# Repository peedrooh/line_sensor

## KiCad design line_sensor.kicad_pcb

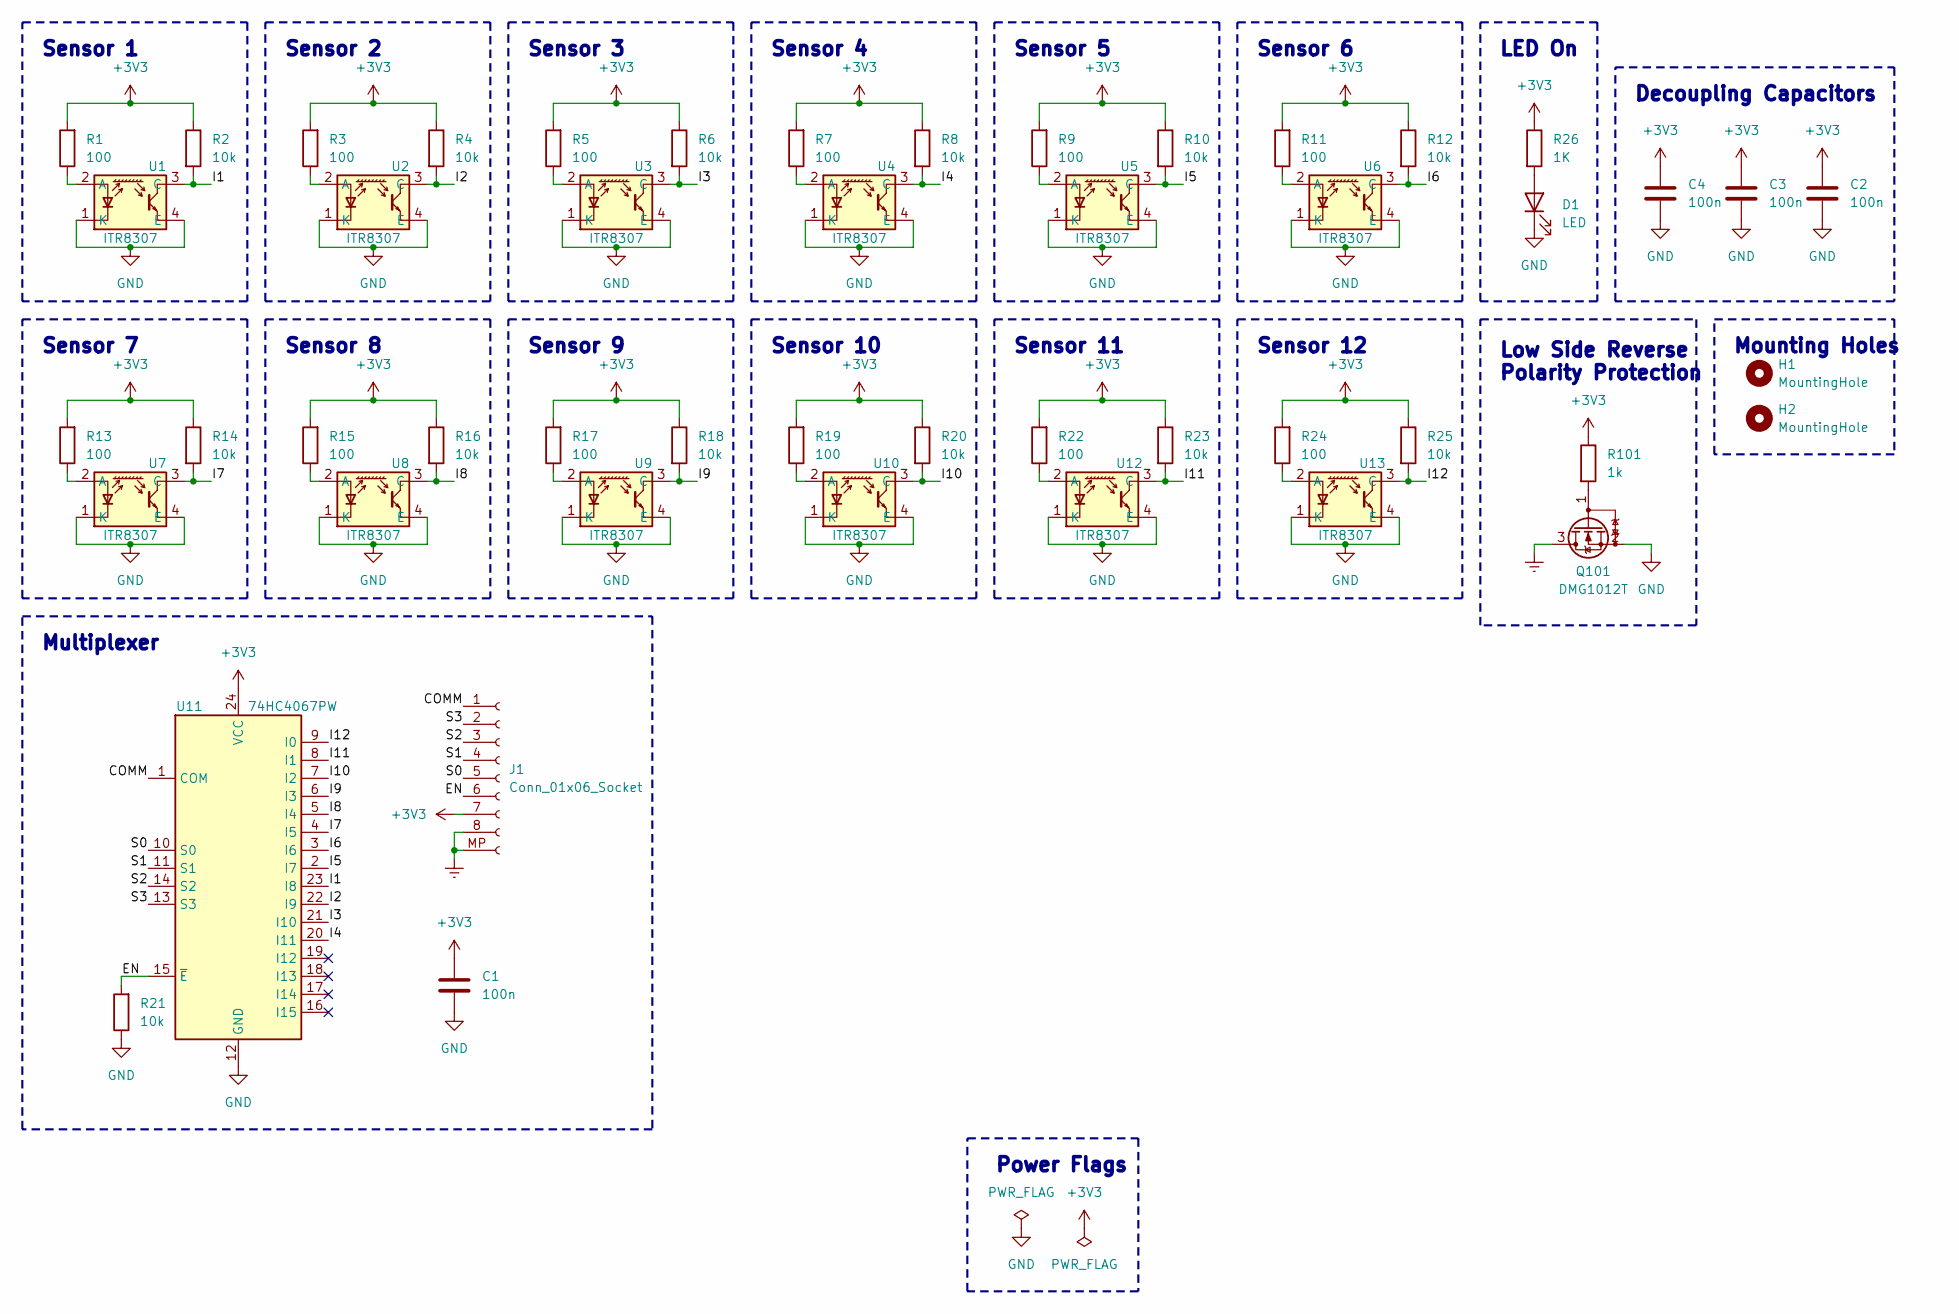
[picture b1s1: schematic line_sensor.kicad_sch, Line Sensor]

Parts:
C1, C2, C3, C4: 100n; C_0805_2012Metric_Pad1.18x1.45mm_HandSolder; LCSC C38141
D1: LED; LED_0805_2012Metric; LCSC C391863
H1, H2: MountingHole; MountingHole_3.2mm_M3_Pad_Via
J1: Conn_01x06_Socket; JST_PH_B8B-PH-SM4-TB_1x08-1MP_P2.00mm_Vertical
Q101: DMG1012T; SOT-523; LCSC C20512
R1, R3, R5, R7, R9, R11, R13, R15, R17, R19, R22, R24: 100; R_0805_2012Metric; LCSC C17408
R2, R4, R8, R10, R12, R14, R16, R18, R20, R21, R23, R25: 10k; R_0805_2012Metric; LCSC C17414
R6: 10k; R_0805_2012Metric; MPN C17414
R26: 1K; R_0805_2012Metric; LCSC C17513
R101: 1k; R_0805_2012Metric; LCSC C17513
U1, U2, U3, U4, U5, U6, U7, U8, U9, U10, U12, U13: ITR8307; ITR8307_S18_TR8_B; LCSC C115037
U11: 74HC4067PW; TSSOP-24_4.4x7.8mm_P0.65mm; LCSC C179326

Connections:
+3V3: C1.1, C2.1, C3.1, C4.1, J1.7, R1.2, R2.1, R3.2, R4.1, R5.2, R6.1, R7.2, R8.1, R9.2, R10.1, R11.2, R12.1, R13.2, R14.1, R15.2, R16.1, R17.2, R18.1, R19.2, R20.1, R22.2, R23.1, R24.2, R25.1, R26.1, R101.1, U11.24 (VCC)
/COMM: J1.1, U11.1 (COM)
/EN: J1.6, R21.2, U11.15 (~E)
/I1: R2.2, U1.3 (C), U11.23 (I8)
/I2: R4.2, U2.3 (C), U11.22 (I9)
/I3: R6.2, U3.3 (C), U11.21 (I10)
/I4: R8.2, U4.3 (C), U11.20 (I11)
/I5: R10.2, U5.3 (C), U11.2 (I7)
/I6: R12.2, U6.3 (C), U11.3 (I6)
/I7: R14.2, U7.3 (C), U11.4 (I5)
/I8: R16.2, U8.3 (C), U11.5 (I4)
/I9: R18.2, U9.3 (C), U11.6 (I3)
/I10: R20.2, U10.3 (C), U11.7 (I2)
/I11: R23.2, U11.8 (I1), U12.3 (C)
/I12: R25.2, U11.9 (I0), U13.3 (C)
/S0: J1.5, U11.10 (S0)
/S1: J1.4, U11.11 (S1)
/S2: J1.3, U11.14 (S2)
/S3: J1.2, U11.13 (S3)
Earth: J1.8, J1.MP (Pin_9), Q101.3 (D)
GND: C1.2, C2.2, C3.2, C4.2, D1.1 (K), Q101.2 (S), R21.1, U1.1 (K), U1.4 (E), U2.1 (K), U2.4 (E), U3.1 (K), U3.4 (E), U4.1 (K), U4.4 (E), U5.1 (K), U5.4 (E), U6.1 (K), U6.4 (E), U7.1 (K), U7.4 (E), U8.1 (K), U8.4 (E), U9.1 (K), U9.4 (E), U10.1 (K), U10.4 (E), U11.12 (GND), U12.1 (K), U12.4 (E), U13.1 (K), U13.4 (E)
unnamed: D1.2 (A), R26.2
unnamed: Q101.1 (G), R101.2
unnamed: R1.1, U1.2 (A)
unnamed: R3.1, U2.2 (A)
unnamed: R5.1, U3.2 (A)
unnamed: R7.1, U4.2 (A)
unnamed: R9.1, U5.2 (A)
unnamed: R11.1, U6.2 (A)
unnamed: R13.1, U7.2 (A)
unnamed: R15.1, U8.2 (A)
unnamed: R17.1, U9.2 (A)
unnamed: R19.1, U10.2 (A)
unnamed: R22.1, U12.2 (A)
unnamed: R24.1, U13.2 (A)

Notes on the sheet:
Sensor 7
Sensor 10
Mounting Holes
LED On
Sensor 11
Power Flags
Sensor 4
Sensor 2
Sensor 12
Sensor 3
Sensor 5
Decoupling Capacitors
Multiplexer
Low Side Reverse Polarity Protection
Sensor 6
Sensor 9
Sensor 1
Sensor 8

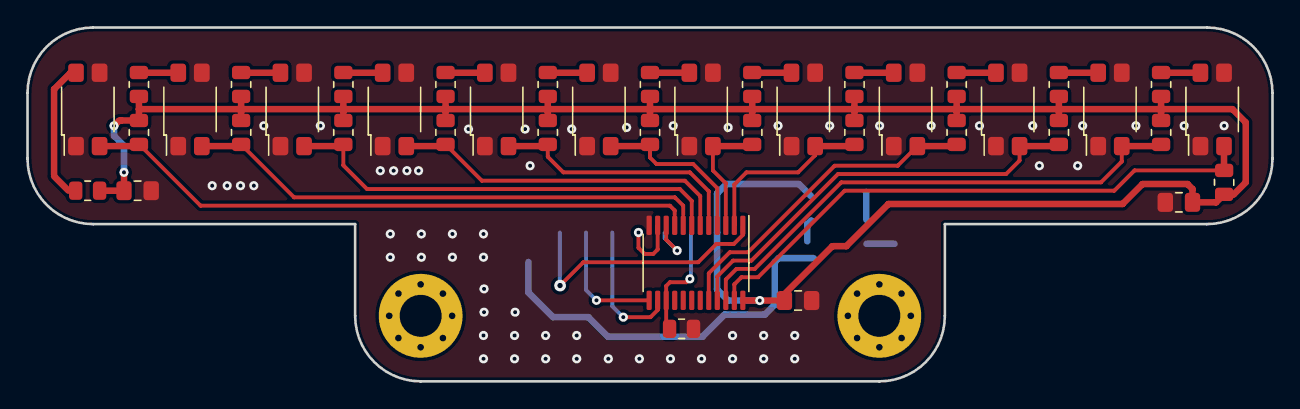
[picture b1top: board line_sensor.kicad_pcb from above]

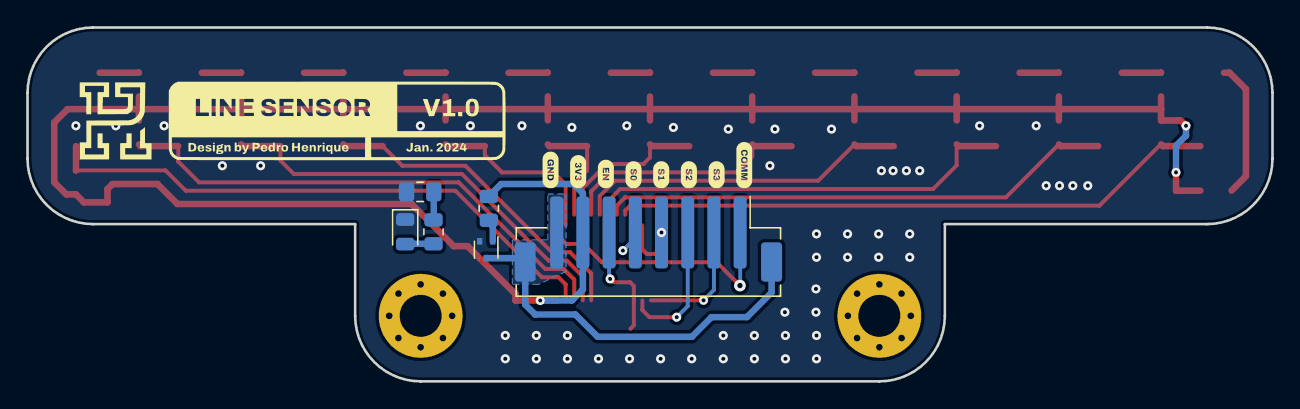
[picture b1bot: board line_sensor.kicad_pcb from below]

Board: 2 copper layers, 95.0 x 27.0 mm, 49 parts (6 on the bottom side), 35 nets.
